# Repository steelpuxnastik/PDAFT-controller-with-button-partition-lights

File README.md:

# PDAFT controller with button/partition lights

## What is it?
Hatsune Miku Project DIVA Arcade Future Tone controller with button/partition lights support (works fully like on official arcade machine) controlled by game. Controller realizes work with buttons (TRIANGLE, SQUARE, CROSS, CIRCLE, START) and abitily to connect 4 buttons LED and left/right partition 12V RGB LED strip (without slider, for slider I recomend to use LKP https://github.com/Project-Alpaca/LKP). LED info obtained by UART, special PD-Loader plugin activation needed (coming soon).

## Repository contains
Contains [PCB](/PDAFT_BPL_PCB) (KiCad 5.99+  (5.99.0-11737-gca42f31bb5), release build or newer needs to open) and [firmware](/firmware) for Arduino Pro Micro that used in it (use Arduino IDE 1.8 or newer to flash firmware).

## Variations
Board has two possibilities to receive serial data: throught USB (serial) or using TTL (serial1).
Why is that? Because ATMEGA32U4 chip directly supports USB connections and supports USB-Serial connection, but USB-Serial doesn't supports interuptions. Interuptions can be realized only throught direct connection to RX/TX pins using, for example, USB-TTL converter. It theoreticaly can make using gamepad without delays and Serial1 will be used only when new data will appear, but in real work with Serial data optimized as far as I know at this moment and works very fast (direct write to registers used), so needs only few cycles to work with that, so in reality maybe there will be no difference in use USB-Serial or TTL.

To use USB-Serial connection flash `firmware/firmware_USB-Serial/firmware_USB-Serial.ino`

To use TTL - `firmware/firmware_TTL/firmware_TTL.ino`

## Parts needed to use

`PDAFT_BPL_PCB` (1 pcs, order on JLCPCB or somewhere else or make it by yourself)

`JST XH 2pin socket and plug` (5 pcs) for:
  - Start button (desctibed pins from 1 to last, `OUT`, `GND`)
  - Triangle button LED (`+`, `-`)
  - Square button LED (`+`, `-`)
  - Cross button LED (`+`, `-`)
  - Circle button LED (`+`, `-`)

`JST XH 3pin socket and plug` (4 pcs) for:
  - Triangle button (`OUT`, `+` , `-`)
  - Square button (`OUT`, `+` , `-`)
  - Cross button (`OUT`, `+` , `-`)
  - Circle button (`OUT`, `+` , `-`)

`JST XH 4pin socket and plug` (4 pcs)
  - Partition RGB Left (`+12v`, `G`, `R`, `B`)
  - Partition RGB Right (`+12v`, `G`, `R`, `B`)
  - TTL (`RX`, `TX`, `GND`, `+5v`. Do not use 4 pin `+5V` if you connect Arduino with USB)
  - 12V IN (`+`, `+`, `-`,`-`. JST XH connection by datasheet has 3A current rating limitation on one pin, if you'll use long stripes with a lot of LEDs, most likely current will be somewhere around or more then 3A, so better to make paralelized connection to board with two 22 AWG or thicker wire for `12V` (`+`) and `GND` (`-`) from the power socket to board. *I'll uploud picture later about that for you to understand*)
  
 `Arduino ProMicro` (1 pcs)
 
 `12 pin header` (2 pcs, to have possibility to just plug in Arduino ProMicro and change it if needed without soldering, `12 pin header` will be soldered)
 
 `ULN2003` (2 pcs, to use LEDs with it)
 
 `DIP 16 pin socket` (2 pcs, to make possibility to change `ULN2003` without soldering if needed, `DIP 16 pin socket` will be soldered)
 
 `22 AWG wires` (can be found on aliexpress, I recommend to grab more 5 pin 22 AWG white-blue-red-green-black cable, if you use [SHINSANWASWITCH](https://github.com/steelpuxnastik/SHINSANWASWITCH) it will be usefull too)

## About button connection

By default assumed that you will connect active optical switches ([SHINSANWASWITCH](https://github.com/steelpuxnastik/SHINSANWASWITCH) or OBSA-LHSXF-LN or other) as Triangle, Square, Cross, Circle buttons. If you want to connect passive switches - use connection only to 1 pin (`OUT`) and 3 pin (`-`) and connect nothing to 2 pin (`+`).

## Work in progress

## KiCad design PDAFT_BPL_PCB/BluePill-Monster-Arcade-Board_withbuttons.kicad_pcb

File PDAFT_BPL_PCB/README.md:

KICAD Version: (5.99.0-11575-g46338403e7), release build or newer needed to open files

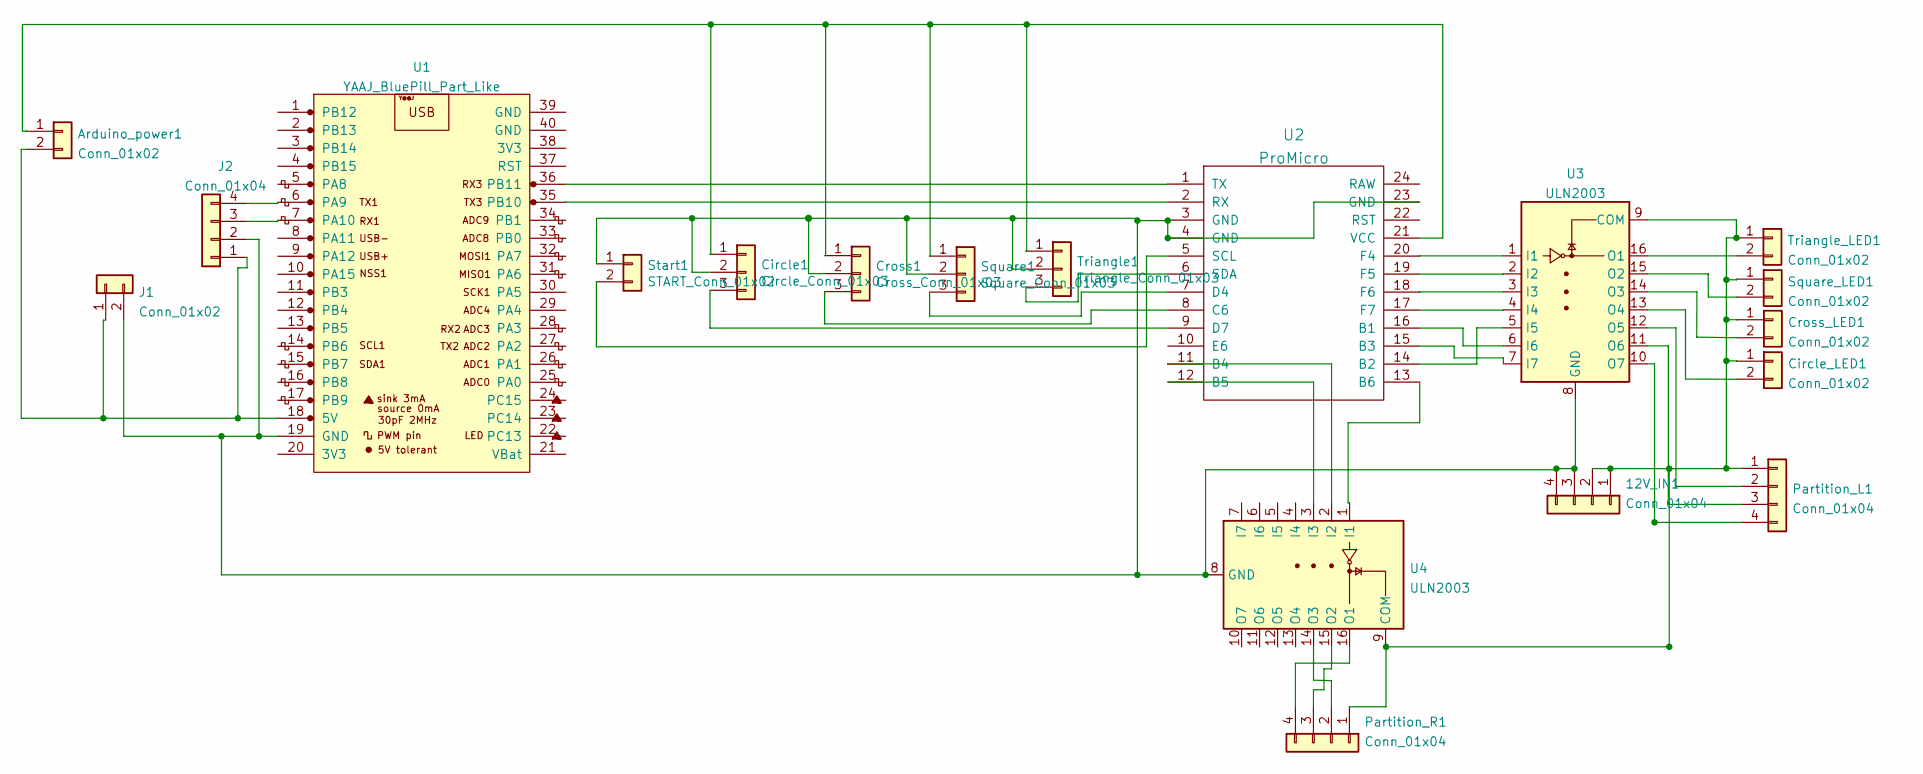
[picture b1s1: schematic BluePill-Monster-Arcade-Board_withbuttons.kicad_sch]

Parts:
12V_IN1: Conn_01x04; JST_XH_B4B-XH-A_1x04_P2.50mm_Vertical
Arduino_power1: Conn_01x02; JST_XH_B2B-XH-A_1x02_P2.50mm_Vertical
Circle1: Circle_Conn_01x03; JST_XH_B3B-XH-A_1x03_P2.50mm_Vertical
Circle_LED1: Conn_01x02; JST_XH_B2B-XH-A_1x02_P2.50mm_Vertical
Cross1: Cross_Conn_01x03; JST_XH_B3B-XH-A_1x03_P2.50mm_Vertical
Cross_LED1: Conn_01x02; JST_XH_B2B-XH-A_1x02_P2.50mm_Vertical
J1: Conn_01x02; JST_XH_B2B-XH-A_1x02_P2.50mm_Vertical
J2: Conn_01x04; JST_XH_B4B-XH-A_1x04_P2.50mm_Vertical
Partition_L1: Conn_01x04; JST_XH_B4B-XH-A_1x04_P2.50mm_Vertical
Partition_R1: Conn_01x04; JST_XH_B4B-XH-A_1x04_P2.50mm_Vertical
Square1: Square_Conn_01x03; JST_XH_B3B-XH-A_1x03_P2.50mm_Vertical
Square_LED1: Conn_01x02; JST_XH_B2B-XH-A_1x02_P2.50mm_Vertical
Start1: START_Conn_01x02; JST_XH_B2B-XH-A_1x02_P2.50mm_Vertical
Triangle1: Triangle_Conn_01x03; JST_XH_B3B-XH-A_1x03_P2.50mm_Vertical
Triangle_LED1: Conn_01x02; JST_XH_B2B-XH-A_1x02_P2.50mm_Vertical
U1: YAAJ_BluePill_Part_Like; YAAJ_BluePill_1
U2: ProMicro
U3, U4: ULN2003; DIP-16_W7.62mm

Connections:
unnamed: 12V_IN1.1, 12V_IN1.2, Circle_LED1.1, Cross_LED1.1, Partition_L1.1, Partition_R1.1, Square_LED1.1, Triangle_LED1.1, U3.9 (COM), U4.9 (COM)
unnamed: 12V_IN1.3, 12V_IN1.4, Circle1.2, Cross1.2, J1.2, J2.2, Square1.2, Start1.1, Triangle1.2, U1.19 (GND), U2.3 (GND), U2.4 (GND), U2.23 (GND), U3.8 (GND), U4.8 (GND)
unnamed: Arduino_power1.1, Circle1.1, Cross1.1, Square1.1, Triangle1.1, U2.21 (VCC)
unnamed: Arduino_power1.2, J1.1, J2.1, U1.18 (5V)
unnamed: Circle1.3, U2.9 (D7)
unnamed: Circle_LED1.2, U3.13 (O4)
unnamed: Cross1.3, U2.8 (C6)
unnamed: Cross_LED1.2, U3.14 (O3)
unnamed: J2.3, U1.7 (PA10)
unnamed: J2.4, U1.6 (PA9)
unnamed: Partition_L1.2, U3.12 (O5)
unnamed: Partition_L1.3, U3.11 (O6)
unnamed: Partition_L1.4, U3.10 (O7)
unnamed: Partition_R1.2, U4.14 (O3)
unnamed: Partition_R1.3, U4.15 (O2)
unnamed: Partition_R1.4, U4.16 (O1)
unnamed: Square1.3, U2.7 (D4)
unnamed: Square_LED1.2, U3.15 (O2)
unnamed: Start1.2, U2.5 (SCL)
unnamed: Triangle1.3, U2.6 (SDA)
unnamed: Triangle_LED1.2, U3.16 (O1)
unnamed: U1.35 (PB10), U2.2 (RX)
unnamed: U1.36 (PB11), U2.1 (TX)
unnamed: U2.11 (B4), U4.2 (I2)
unnamed: U2.12 (B5), U4.3 (I3)
unnamed: U2.13 (B6), U4.1 (I1)
unnamed: U2.14 (B2), U3.5 (I5)
unnamed: U2.15 (B3), U3.7 (I7)
unnamed: U2.16 (B1), U3.6 (I6)
unnamed: U2.17 (F7), U3.4 (I4)
unnamed: U2.18 (F6), U3.3 (I3)
unnamed: U2.19 (F5), U3.2 (I2)
unnamed: U2.20 (F4), U3.1 (I1)

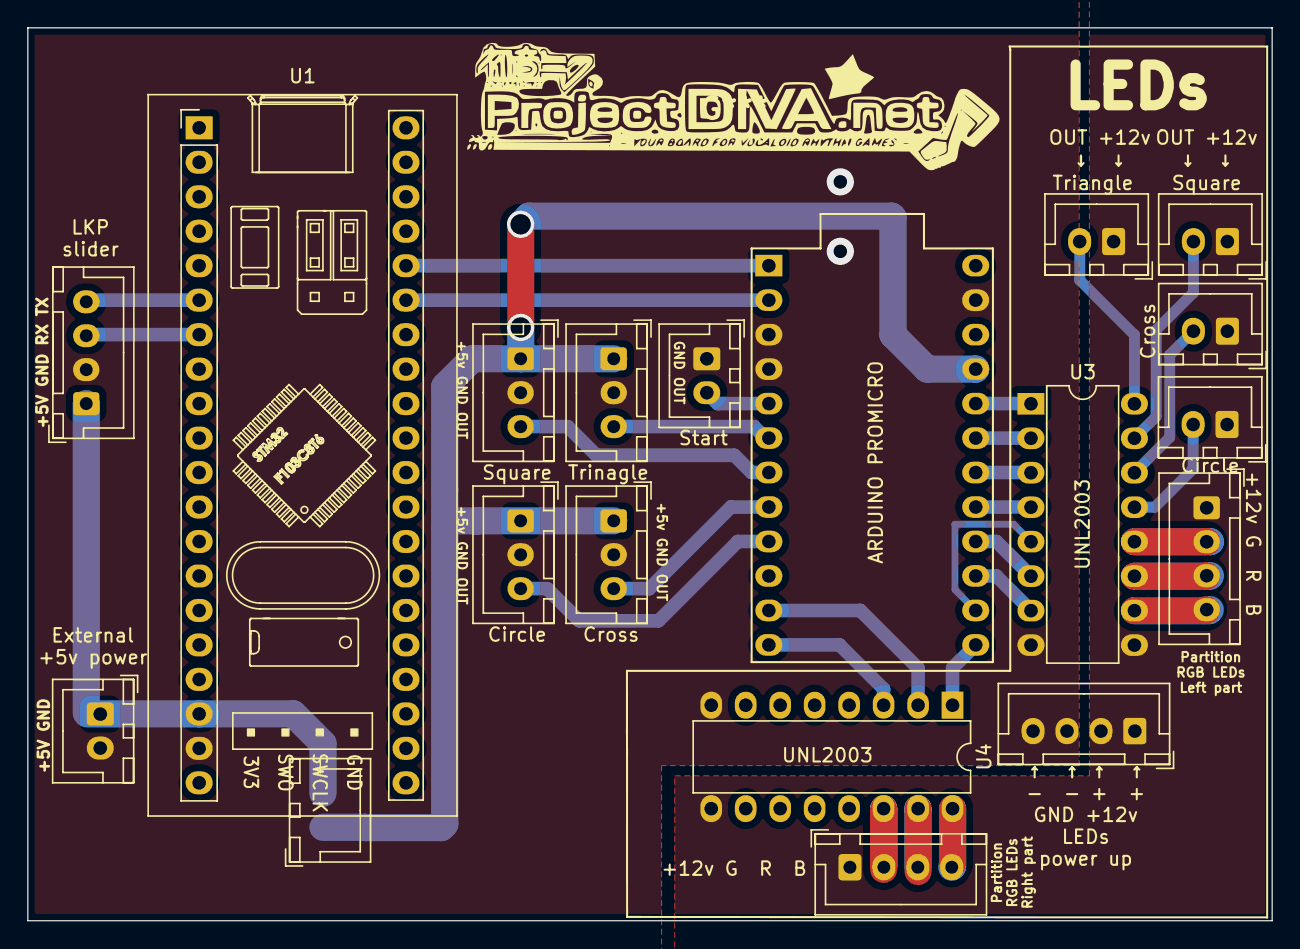
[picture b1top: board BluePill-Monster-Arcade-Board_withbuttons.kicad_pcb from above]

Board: 2 copper layers, 91.7 x 65.8 mm, 19 parts (0 on the bottom side), 33 nets.

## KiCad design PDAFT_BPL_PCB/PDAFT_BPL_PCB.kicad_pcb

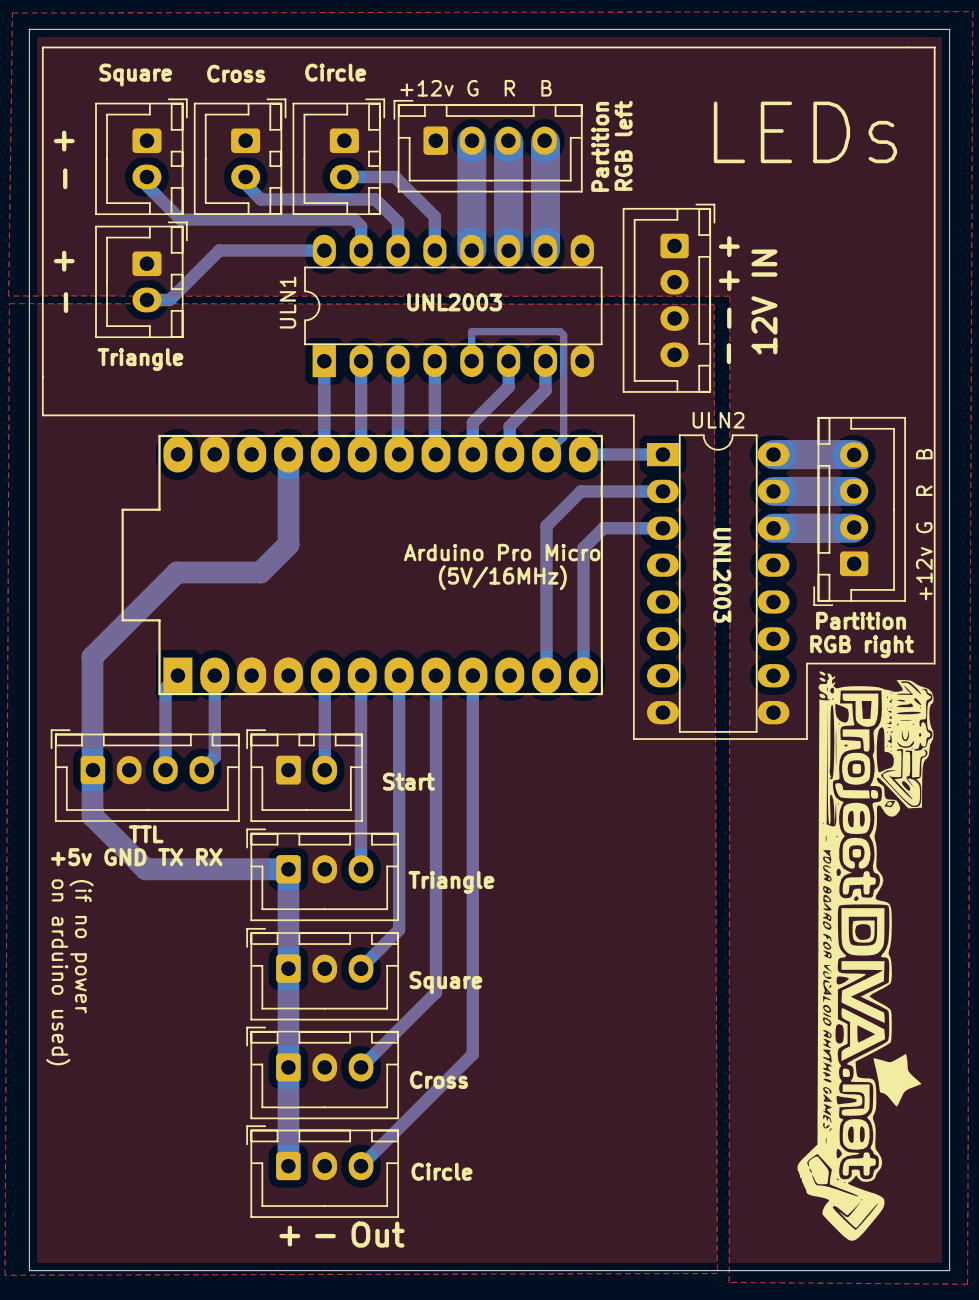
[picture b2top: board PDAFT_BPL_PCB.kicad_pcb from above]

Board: 2 copper layers, 63.4 x 85.5 mm, 16 parts (0 on the bottom side), 30 nets.

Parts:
12V_IN1: 12V_IN; JST_XH_B4B-XH-A_1x04_P2.50mm_Vertical
CIRCLE_LED1: CIRCLE_LED_Conn_01x02; JST_XH_B2B-XH-A_1x02_P2.50mm_Vertical
CROSS_LED1: CROSS_LED_Conn_01x02; JST_XH_B2B-XH-A_1x02_P2.50mm_Vertical
Circle1: Circle_Conn_01x03; JST_XH_B3B-XH-A_1x03_P2.50mm_Vertical
Cross1: Cross_Conn_01x03; JST_XH_B3B-XH-A_1x03_P2.50mm_Vertical
Partition_L1: Conn_01x04; JST_XH_B4B-XH-A_1x04_P2.50mm_Vertical
Partition_R1: Conn_01x04; JST_XH_B4B-XH-A_1x04_P2.50mm_Vertical
ProMicro1: ProMicro
SQUARE_LED1: SQUARE_LED_Conn_01x02; JST_XH_B2B-XH-A_1x02_P2.50mm_Vertical
Square1: Square_Conn_01x03; JST_XH_B3B-XH-A_1x03_P2.50mm_Vertical
Start1: START_Conn_01x02; JST_XH_B2B-XH-A_1x02_P2.50mm_Vertical
TRIANGLE_LED1: TRIANGLE_LED_Conn_01x02; JST_XH_B2B-XH-A_1x02_P2.50mm_Vertical
TTL1: Conn_01x04; JST_XH_B4B-XH-A_1x04_P2.50mm_Vertical
Triangle1: Triangle_Conn_01x03; JST_XH_B3B-XH-A_1x03_P2.50mm_Vertical
ULN1, ULN2: ULN2003; DIP-16_W7.62mm

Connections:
unnamed: 12V_IN1.1, 12V_IN1.2, CIRCLE_LED1.1, CROSS_LED1.1, Partition_L1.1, Partition_R1.1, SQUARE_LED1.1, TRIANGLE_LED1.1, ULN1.9 (COM), ULN2.9 (COM)
unnamed: 12V_IN1.3, 12V_IN1.4, Circle1.2, Cross1.2, ProMicro1.3 (GND), ProMicro1.4 (GND), ProMicro1.23 (GND), Square1.2, Start1.1, TTL1.2, Triangle1.2, ULN1.8 (GND), ULN2.8 (GND)
unnamed: CIRCLE_LED1.2, ULN1.13 (O4)
unnamed: CROSS_LED1.2, ULN1.14 (O3)
unnamed: Partition_L1.2, ULN1.12 (O5)
unnamed: Partition_L1.3, ULN1.11 (O6)
unnamed: Partition_L1.4, ULN1.10 (O7)
unnamed: Partition_R1.2, ULN2.14 (O3)
unnamed: Partition_R1.3, ULN2.15 (O2)
unnamed: Partition_R1.4, ULN2.16 (O1)
unnamed: ProMicro1.5 (SCL), Start1.2
unnamed: ProMicro1.6 (SDA), Triangle1.3
unnamed: ProMicro1.7 (D4), Square1.3
unnamed: Cross1.3, ProMicro1.8 (C6)
unnamed: Circle1.3, ProMicro1.9 (D7)
unnamed: ProMicro1.11 (B4), ULN2.2 (I2)
unnamed: ProMicro1.12 (B5), ULN2.3 (I3)
unnamed: ProMicro1.13 (B6), ULN2.1 (I1)
unnamed: ProMicro1.14 (B2), ULN1.5 (I5)
unnamed: ProMicro1.15 (B3), ULN1.7 (I7)
unnamed: ProMicro1.16 (B1), ULN1.6 (I6)
unnamed: ProMicro1.17 (F7), ULN1.4 (I4)
unnamed: ProMicro1.18 (F6), ULN1.3 (I3)
unnamed: ProMicro1.19 (F5), ULN1.2 (I2)
unnamed: ProMicro1.20 (F4), ULN1.1 (I1)
unnamed: Circle1.1, Cross1.1, ProMicro1.21 (VCC), Square1.1, TTL1.1, Triangle1.1
unnamed: SQUARE_LED1.2, ULN1.15 (O2)
unnamed: TRIANGLE_LED1.2, ULN1.16 (O1)
unnamed: ProMicro1.1 (TX), TTL1.3
unnamed: ProMicro1.2 (RX), TTL1.4

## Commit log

2021-07-29 Kicad board and test firmware added
2021-07-29 readme from old board detele :)
2021-07-30 Update PCB
    Update PCB to make fast write to registers in interruptions when received LEDs data by UART
2021-08-04 Update of PCB and firmware
    Updated PCB to have possibility to connect USB-TTL converter to use interuption in serial connection (program for it will be soon completed with various variants of use, now only SerialEvent1() inter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
2021-08-26 Added +5v from TTL to use if needed
2021-08-26 Changing 12vin JST XH2 to XH4
    Changing 12Vin JST XH2 to XH4 because of possible current rating limits 3A, so better to parallelize 12Vin to avoid problems with it
2021-08-26 Firmware update
    Firmware updated (USB-Serial and serial1 different firmware files), added 3D-model of Arduino for picture, pictures added, readme updated
2021-08-26 PCB update
2021-08-27 Additional poligon on the top, other fixes
2021-08-27 Holes correct
2021-08-29 board update
2021-09-03 Update for DIY-make
2021-09-05 Added shorter variant, maybe later it will be main
    Also some elements optimization
2021-09-05 BluePill-moster added
2021-09-05 bluepill update
2021-10-11 Update of bluepill moster with buttons to order on JLCPCB
